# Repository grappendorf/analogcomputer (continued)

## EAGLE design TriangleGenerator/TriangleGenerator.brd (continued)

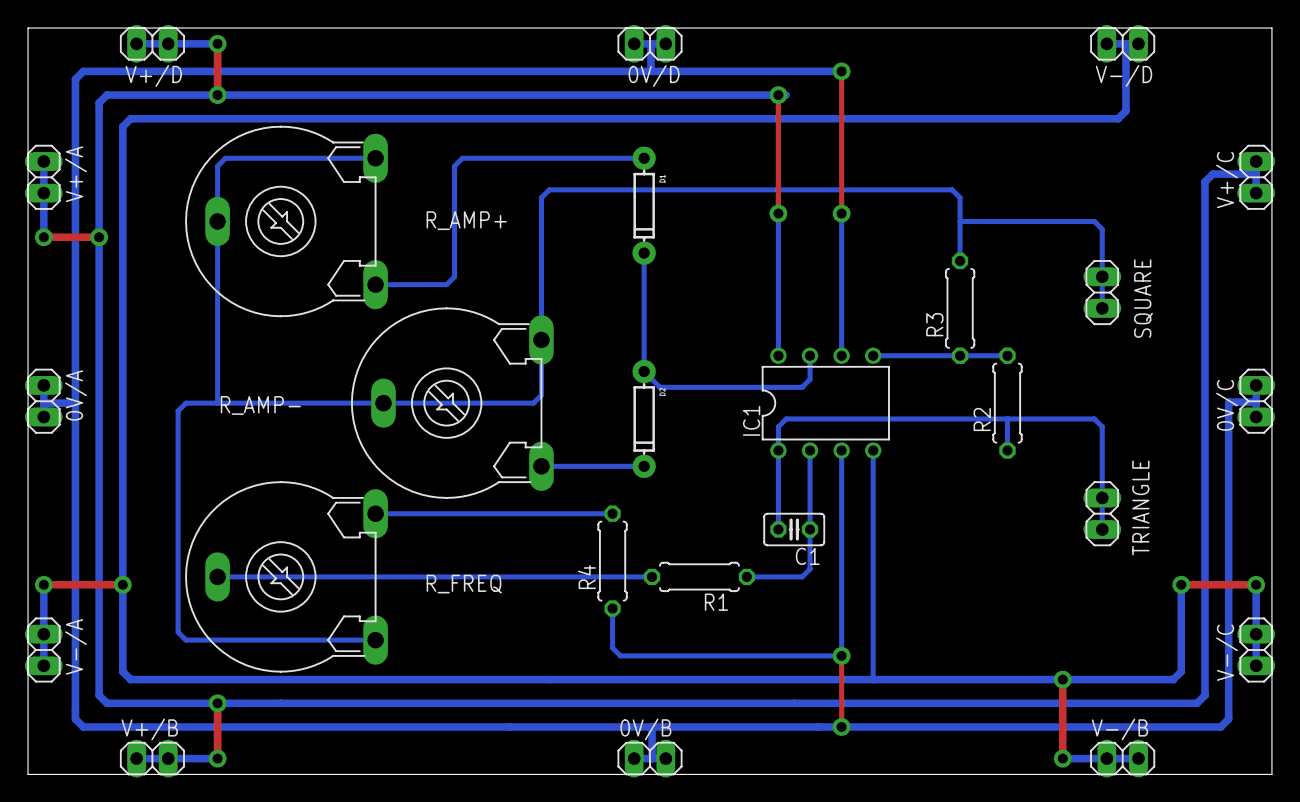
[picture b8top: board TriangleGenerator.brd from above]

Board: 2 copper layers, 100.0 x 60.0 mm, 25 parts (0 on the bottom side), 12 nets.

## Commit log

2015-09-29 Minor fixes
2015-09-29 Add amplifier schematic and board
2015-09-29 Add reference voltage schematic and board
2015-09-29 no longer need a package script
